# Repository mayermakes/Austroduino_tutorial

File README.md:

# Austroduino_tutorial
the result of a Kicad 9 tutorial, arduino compatible Attiny3226 based dev board

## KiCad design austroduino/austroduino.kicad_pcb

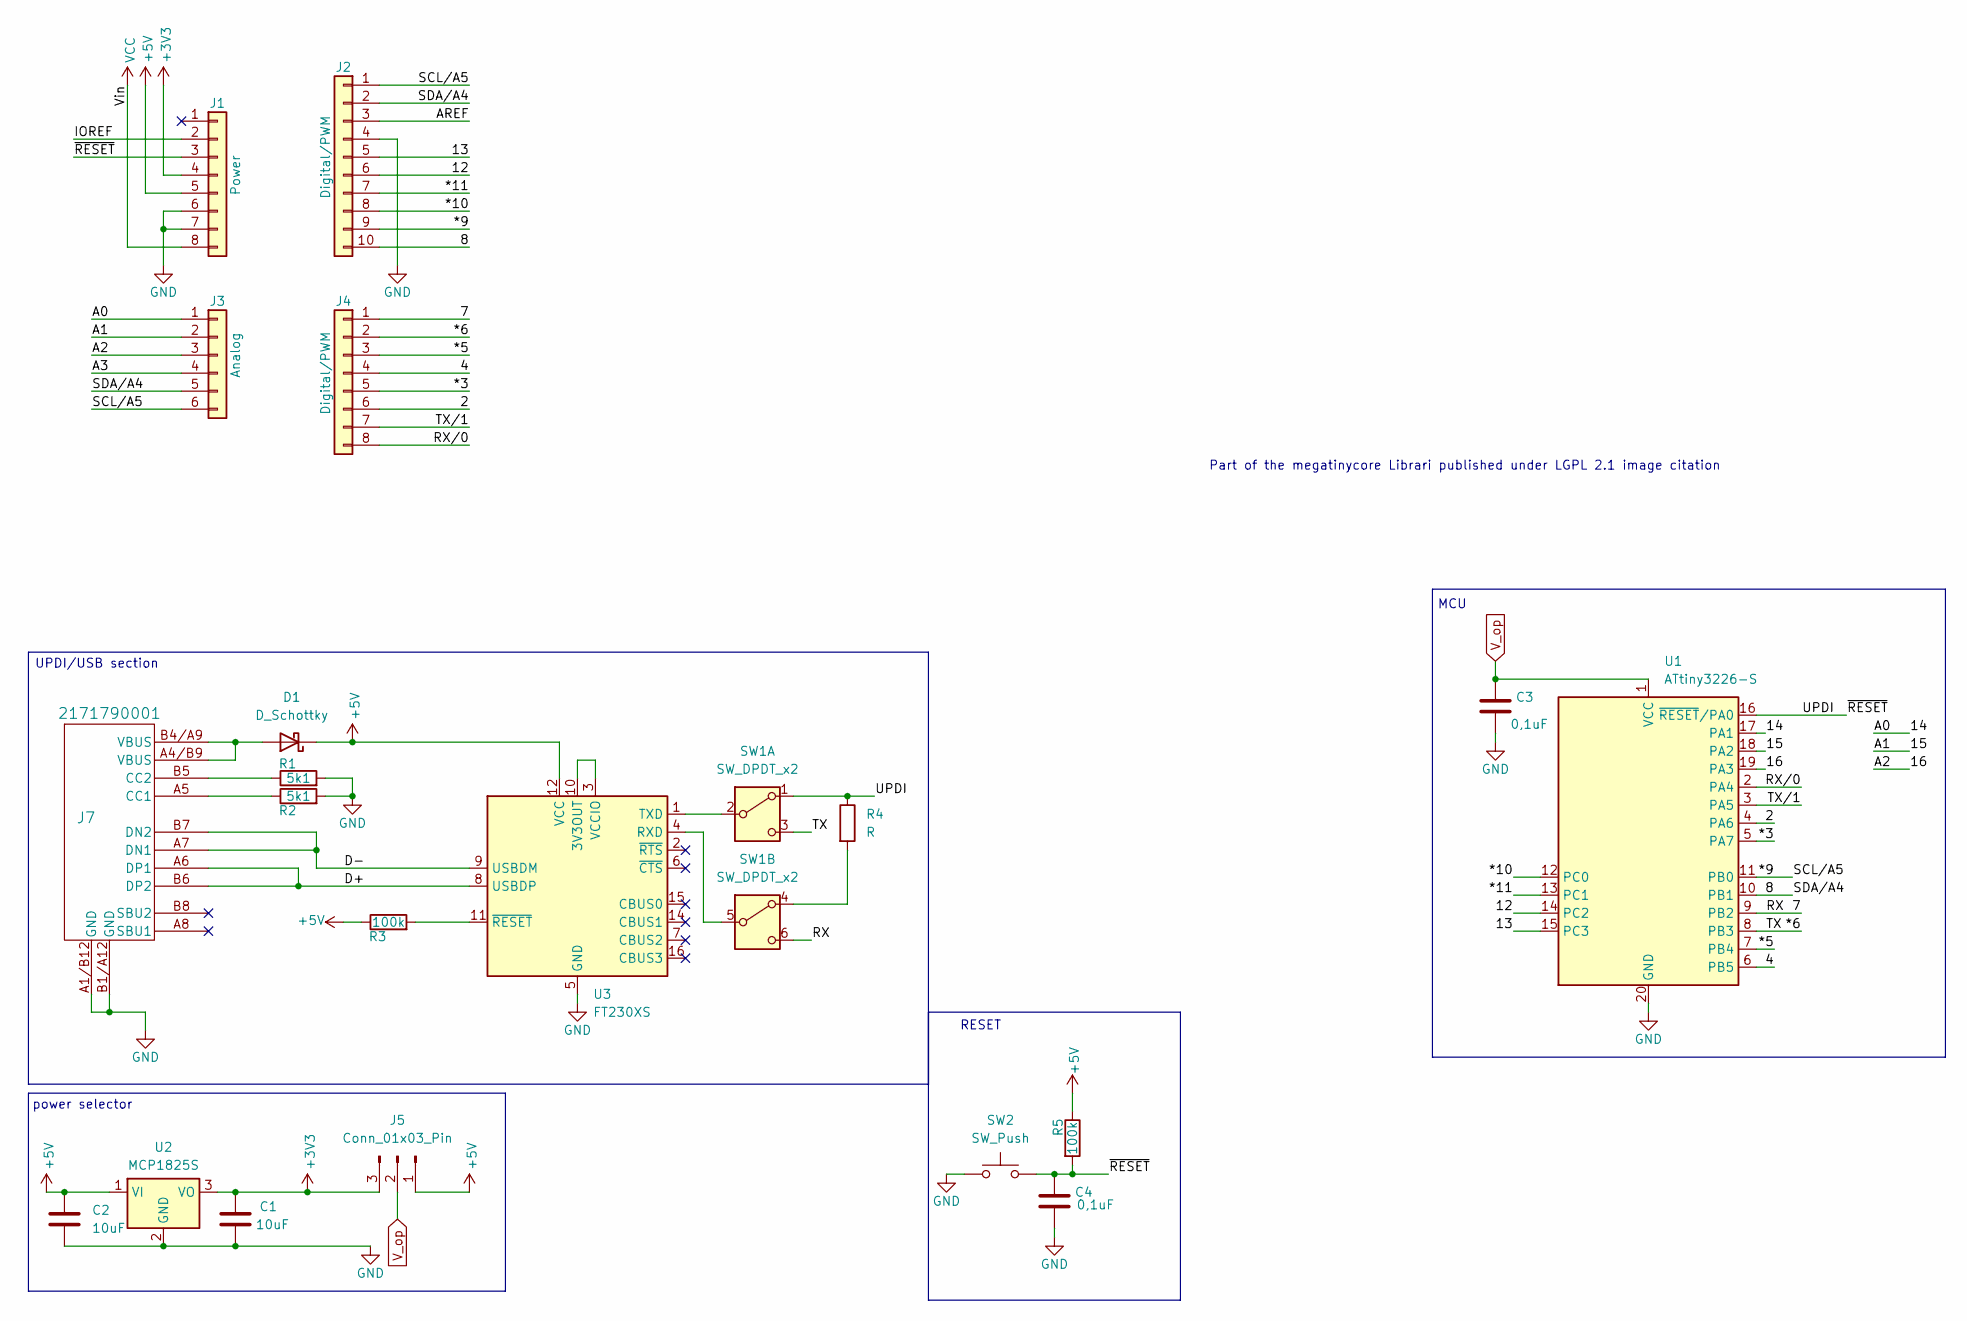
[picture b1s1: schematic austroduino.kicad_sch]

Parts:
C1, C2: 10uF; C_0603_1608Metric
C3, C4: 0,1uF; C_0603_1608Metric
D1: D_Schottky; D_0603_1608Metric_Pad1.05x0.95mm_HandSolder
J1: Power; PinSocket_1x08_P2.54mm_Vertical
J2: Digital/PWM; PinSocket_1x10_P2.54mm_Vertical
J3: Analog; PinSocket_1x06_P2.54mm_Vertical
J4: Digital/PWM; PinSocket_1x08_P2.54mm_Vertical
J5: Conn_01x03_Pin; PinHeader_1x03_P2.54mm_Vertical
J7: 2171790001; 2171790001_MOL
R1, R2: 5k1; R_0603_1608Metric
R3, R5: 100k; R_0603_1608Metric
R4: R; R_0603_1608Metric
SW1: SW_DPDT_x2; SW_DPDT_CK_JS202011JCQN
SW2: SW_Push; SW_SPST_EVQP0
U1: ATtiny3226-S; SOIC-20W_7.5x12.8mm_P1.27mm
U2: MCP1825S; SOT-223-3_TabPin2
U3: FT230XS; SSOP-16_3.9x4.9mm_P0.635mm

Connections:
+3V3: C1.1, J1.4, J5.3, U2.3 (VO)
+5V: C2.1, D1.1 (K), J1.5, J5.1, R3.1, R5.1, U2.1 (VI), U3.12 (VCC)
/2: J4.6, U1.4 (PA6)
/4: J4.4, U1.6 (PB5)
/7: J4.1, SW1.6 (C), U1.9 (PB2)
/8: J2.2, J2.10, J3.5, U1.10 (PB1)
/12: J2.6, U1.14 (PC2)
/13: J2.5, U1.15 (PC3)
/14: J3.1, U1.17 (PA1)
/15: J3.2, U1.18 (PA2)
/16: J3.3, U1.19 (PA3)
/*3: J4.5, U1.5 (PA7)
/*5: J4.3, U1.7 (PB4)
/*6: J4.2, SW1.3 (C), U1.8 (PB3)
/*9: J2.1, J2.9, J3.6, U1.11 (PB0)
/*10: J2.8, U1.12 (PC0)
/*11: J2.7, U1.13 (PC1)
/A3: J3.4
/AREF: J2.3
/D+: J7.A6 (DP1), J7.B6 (DP2), U3.8 (USBDP)
/D-: J7.A7 (DN1), J7.B7 (DN2), U3.9 (USBDM)
/IOREF: J1.2
/RX/0: J4.8, U1.2 (PA4)
/TX/1: J4.7, U1.3 (PA5)
/UPDI: C4.1, J1.3, R4.1, R5.2, SW1.1 (A), SW2.2, U1.16 (~RESET/PA0)
GND: C1.2, C2.2, C3.2, C4.2, J1.6, J1.7, J2.4, J7.A1/B12 (GND), J7.B1/A12 (GND), R1.2, R2.2, SW2.1, U1.20 (GND), U2.2 (GND), U3.5 (GND), U3.13 (GND)
unnamed: D1.2 (A), J7.A4/B9 (VBUS), J7.B4/A9 (VBUS)
unnamed: J7.A5 (CC1), R2.1
unnamed: J7.B5 (CC2), R1.1
unnamed: SW1.2 (B), U3.1 (TXD)
unnamed: R4.2, SW1.4 (A)
unnamed: SW1.5 (B), U3.4 (RXD)
unnamed: U3.3 (VCCIO), U3.10 (3V3OUT)
unnamed: R3.2, U3.11 (~RESET)
VCC: J1.8
V_op: C3.1, J5.2, U1.1 (VCC)

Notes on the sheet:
MCU
UPDI/USB section
RESET
Part of the megatinycore Librari published under LGPL 2.1 image citation
power selector

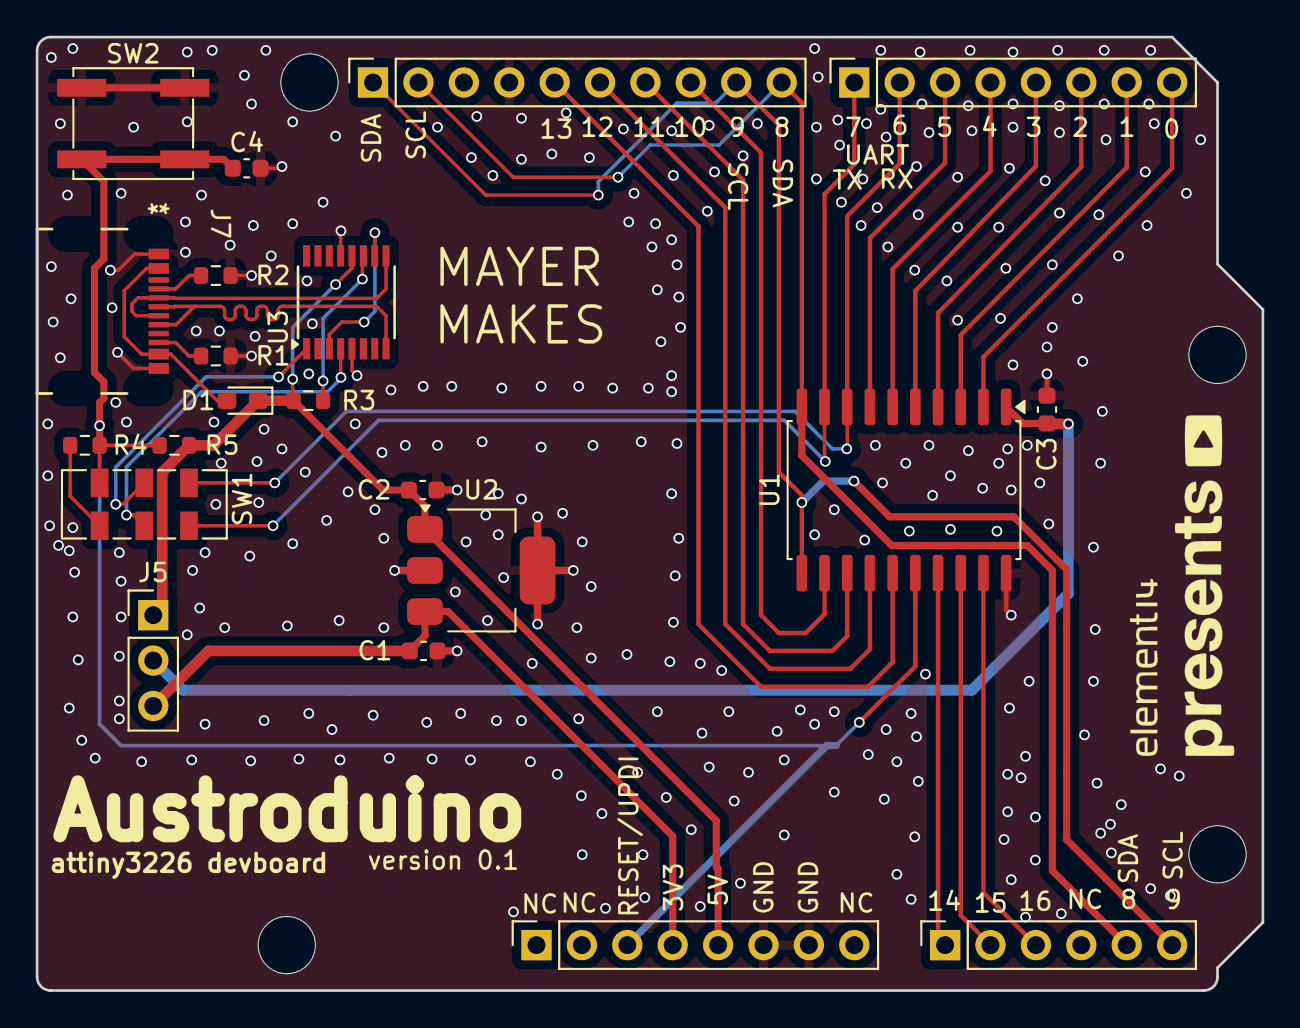
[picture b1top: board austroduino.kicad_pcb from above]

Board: 4 copper layers, 68.6 x 53.3 mm, 27 parts (1 on the bottom side), 32 nets.

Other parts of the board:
MH1, MH2, MH3, MH4: MountingHole_3.2mm
Ref**: Val**; e14presents logo 20mm silk only v1
Ref**#2: Val**; e14presents logo 20mm silk only v1

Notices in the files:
austroduino/austroduino.kicad_pcb:
CC-BY-SA
CC-BY-SA mayermakes 2025
